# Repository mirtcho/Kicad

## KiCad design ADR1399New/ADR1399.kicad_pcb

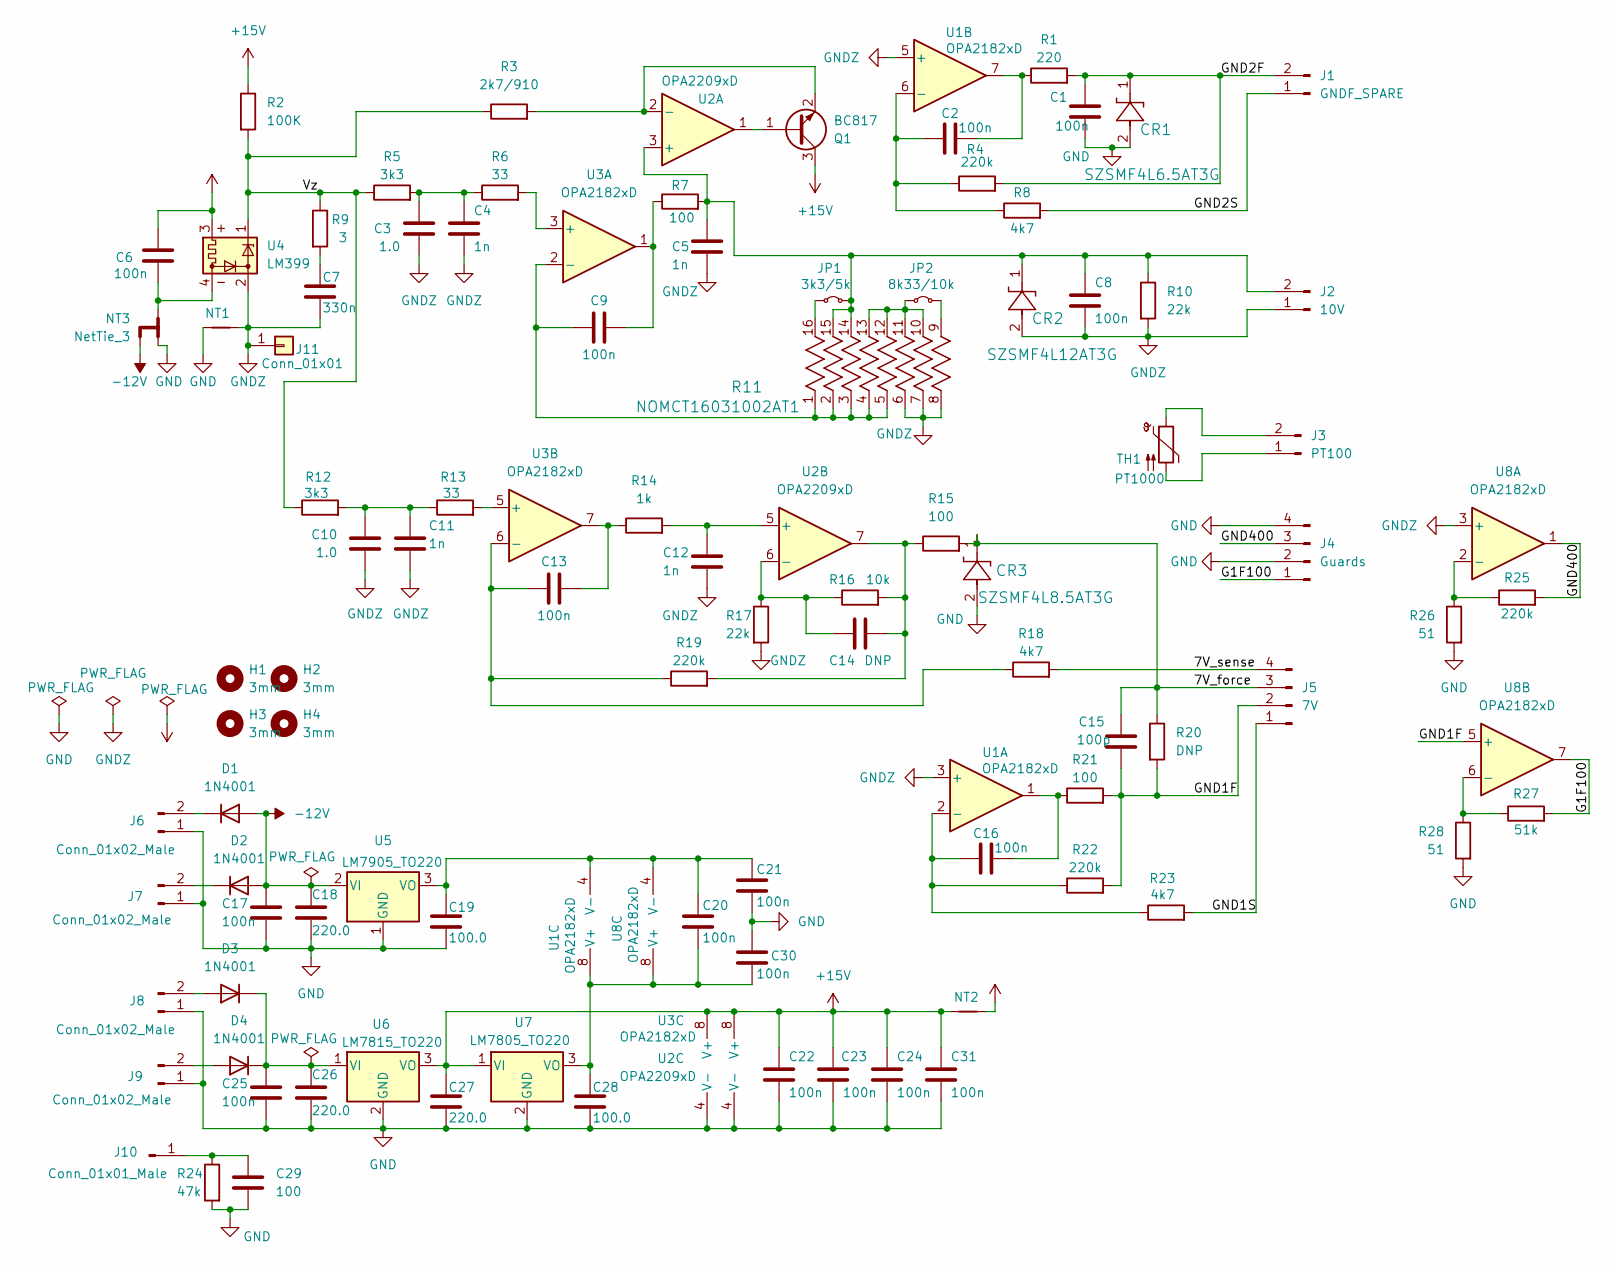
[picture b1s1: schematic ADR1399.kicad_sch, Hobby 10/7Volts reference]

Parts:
C1, C2, C6, C8, C9, C13, C16, C17, C25: 100n; C_1206_3216Metric_Pad1.33x1.80mm_HandSolder
C3, C10: 1.0; C_Rect_L7.2mm_W5.5mm_P5.00mm_FKS2_FKP2_MKS2_MKP2
C4, C11, C12: 1n; C_0805_2012Metric_Pad1.18x1.45mm_HandSolder
C5: 1n; C_1206_3216Metric_Pad1.33x1.80mm_HandSolder
C7: 330n; C_1206_3216Metric_Pad1.33x1.80mm_HandSolder
C14: DNP; C_0805_2012Metric_Pad1.18x1.45mm_HandSolder
C15: 100p; C_1206_3216Metric_Pad1.33x1.80mm_HandSolder
C18, C26, C27: 220.0; CP_Radial_D10.0mm_P7.50mm
C19, C28: 100.0; CP_EIA-3528-12_Kemet-T_HandSolder
C20, C21, C22, C23, C24, C30, C31: 100n; C_0805_2012Metric_Pad1.18x1.45mm_HandSolder
C29: 100; R_1206_3216Metric_Pad1.30x1.75mm_HandSolder
CR1: SZSMF4L6.5AT3G; ZDO_TPSMF4L5.0A_LTF-L
CR2: SZSMF4L12AT3G; ZDO_TPSMF4L5.0A_LTF-L
CR3: SZSMF4L8.5AT3G; ZDO_TPSMF4L5.0A_LTF-L
D1, D2, D3, D4: 1N4001; D_DO-41_SOD81_P10.16mm_Horizontal
H1, H2, H3, H4: 3mm; MountingHole_3.2mm_M3
J1: GNDF_SPARE; PinHeader_1x02_P2.54mm_Vertical
J2: 10V; PinHeader_1x02_P2.54mm_Vertical
J3: PT100; PinHeader_1x02_P2.54mm_Vertical
J4: Guards; PinHeader_2x02_P2.54mm_Vertical
J5: 7V; PinHeader_1x04_P2.54mm_Vertical
J6, J7, J8, J9: Conn_01x02_Male; PinHeader_1x02_P2.54mm_Horizontal
J10: Conn_01x01_Male; PinHeader_1x01_P1.00mm_Vertical
J11: Conn_01x01; SolderWire-1sqmm_1x01_D1.4mm_OD3.9mm
JP1: 3k3/5k; SolderJumper-2_P1.3mm_Bridged2Bar_RoundedPad1.0x1.5mm
JP2: 8k33/10k; SolderJumper-2_P1.3mm_Bridged2Bar_RoundedPad1.0x1.5mm
NT1, NT2: NetTie_2; NetTie-2_SMD_Pad2.0mm
NT3: NetTie_3; SolderJumper-3_P2.0mm_Open_TrianglePad1.0x1.5mm_NumberLabels
Q1: BC817; SOT-23
R1: 220; R_0805_2012Metric_Pad1.20x1.40mm_HandSolder
R2: 100K; R_0805_2012Metric_Pad1.20x1.40mm_HandSolder
R3: 2k7/910; R_1206_3216Metric_Pad1.30x1.75mm_HandSolder
R4, R19, R22, R25: 220k; R_0805_2012Metric_Pad1.20x1.40mm_HandSolder
R5, R12: 3k3; R_0805_2012Metric_Pad1.20x1.40mm_HandSolder
R6, R13: 33; R_0805_2012Metric_Pad1.20x1.40mm_HandSolder
R7, R15, R21: 100; R_0805_2012Metric_Pad1.20x1.40mm_HandSolder
R8, R18, R23: 4k7; R_0805_2012Metric_Pad1.20x1.40mm_HandSolder
R9: 3; R_1206_3216Metric_Pad1.30x1.75mm_HandSolder
R10, R17: 22k; R_0805_2012Metric_Pad1.20x1.40mm_HandSolder
R11: NOMCT16031002AT1; SOIC-16_3.9x9.9mm_P1.27mm
R14: 1k; R_0805_2012Metric_Pad1.20x1.40mm_HandSolder
R16: 10k; R_0805_2012Metric_Pad1.20x1.40mm_HandSolder
R20: DNP; R_0805_2012Metric_Pad1.20x1.40mm_HandSolder
R24: 47k; R_1206_3216Metric_Pad1.30x1.75mm_HandSolder
R26, R28: 51; R_0805_2012Metric_Pad1.20x1.40mm_HandSolder
R27: 51k; R_0805_2012Metric_Pad1.20x1.40mm_HandSolder
TH1: PT1000; PinHeader_1x02_P1.27mm_Vertical
U1, U3, U8: OPA2182xD; SOIC-8_3.9x4.9mm_P1.27mm
U2: OPA2209xD; SOIC-8_3.9x4.9mm_P1.27mm
U4: LM399; Analog_TO-46-4_ThermalShield
U5: LM7905_TO220; TO-220-3_Vertical
U6: LM7815_TO220; TO-220-3_Vertical
U7: LM7805_TO220; TO-220-3_Vertical

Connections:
+15V: C22.1, C23.1, C24.1, C27.1, C31.1, NT2.1, Q1.3 (C), R2.1, U2.8 (V+), U3.8 (V+), U6.3 (VO), U7.1 (VI)
+24V: C6.1, NT2.2, U4.3
-12V: C17.1, C18.1, D1.2 (A), D2.2 (A), NT3.3, U5.2 (VI)
/7V_force: C15.1, CR3.1, J5.3, R15.2, R20.1
/7V_sense: J5.4, R18.2
/G1F100: J4.1, R27.2, U8.7
/GND1F: C15.2, J5.2, R20.2, R21.2, R22.2, U8.5 (+)
/GND1S: J5.1, R23.2
/GND2F: C1.1, CR1.1, J1.2, R1.2, R4.2
/GND2S: J1.1, R8.2
/GND400: J4.3, R25.2, U8.1
/Vz: R2.2, R3.1, R5.1, R9.1, R12.1, U4.1
GND: C1.2, C17.2, C18.2, C19.2, C21.2, C22.2, C23.2, C24.2, C25.2, C26.2, C27.2, C28.2, C29.2, C30.1, C31.2, CR1.2, CR3.2, J4.2, J4.4, J6.1, J7.1, J8.1, J9.1, NT1.1, NT3.1, R24.2, R26.2, R28.2, U2.4 (V-), U3.4 (V-), U5.1 (GND), U6.2 (GND), U7.2 (GND)
GNDZ: C3.1, C4.2, C5.2, C7.2, C8.2, C10.1, C11.2, C12.2, CR2.2, J2.1, J11.1, NT1.2, R10.2, R11.6, R11.7, R11.8, R17.2, U1.3 (+), U1.5 (+), U4.2, U8.3 (+)
unnamed: C2.2, R1.1, U1.7
unnamed: C3.2, C4.1, R5.2, R6.1
unnamed: C6.2, NT3.2, U4.4
unnamed: C7.1, R9.2
unnamed: C9.1, R7.1, U3.1
unnamed: C10.2, C11.1, R12.2, R13.1
unnamed: C13.2, R14.1, U3.7
unnamed: C14.2, R15.1, R16.2, R19.2, U2.7
unnamed: C16.2, R21.1, U1.1
unnamed: D1.1 (K), J6.2
unnamed: D2.1 (K), J7.2
unnamed: D3.2 (A), J8.2
unnamed: C25.1, C26.1, D3.1 (K), D4.1 (K), U6.1 (VI)
unnamed: D4.2 (A), J9.2
unnamed: C5.1, C8.1, CR2.1, J2.2, JP1.2 (B), R7.2, R10.1, R11.14, R11.15, U2.3 (+)
unnamed: J3.1, TH1.2
unnamed: J3.2, TH1.1
unnamed: C29.1, J10.1, R24.1
unnamed: JP1.1 (A), R11.16
unnamed: JP2.1 (A), R11.10, R11.11, R11.12, R11.13
unnamed: JP2.2 (B), R11.9
unnamed: Q1.1 (B), U2.1
unnamed: Q1.2 (E), R3.2, U2.2 (-)
unnamed: C16.1, R22.1, R23.1, U1.2 (-)
unnamed: C2.1, R4.1, R8.1, U1.6 (-)
unnamed: C20.2, C28.1, C30.2, U1.8 (V+), U7.3 (VO), U8.8 (V+)
unnamed: C19.1, C20.1, C21.1, U1.4 (V-), U5.3 (VO), U8.4 (V-)
unnamed: C12.1, R14.2, U2.5 (+)
unnamed: C14.1, R16.1, R17.1, U2.6 (-)
unnamed: R6.2, U3.3 (+)
unnamed: C9.2, R11.1, R11.2, R11.3, R11.4, R11.5, U3.2 (-)
unnamed: R13.2, U3.5 (+)
unnamed: C13.1, R18.1, R19.1, U3.6 (-)
unnamed: R25.1, R26.1, U8.2 (-)
unnamed: R27.1, R28.1, U8.6 (-)

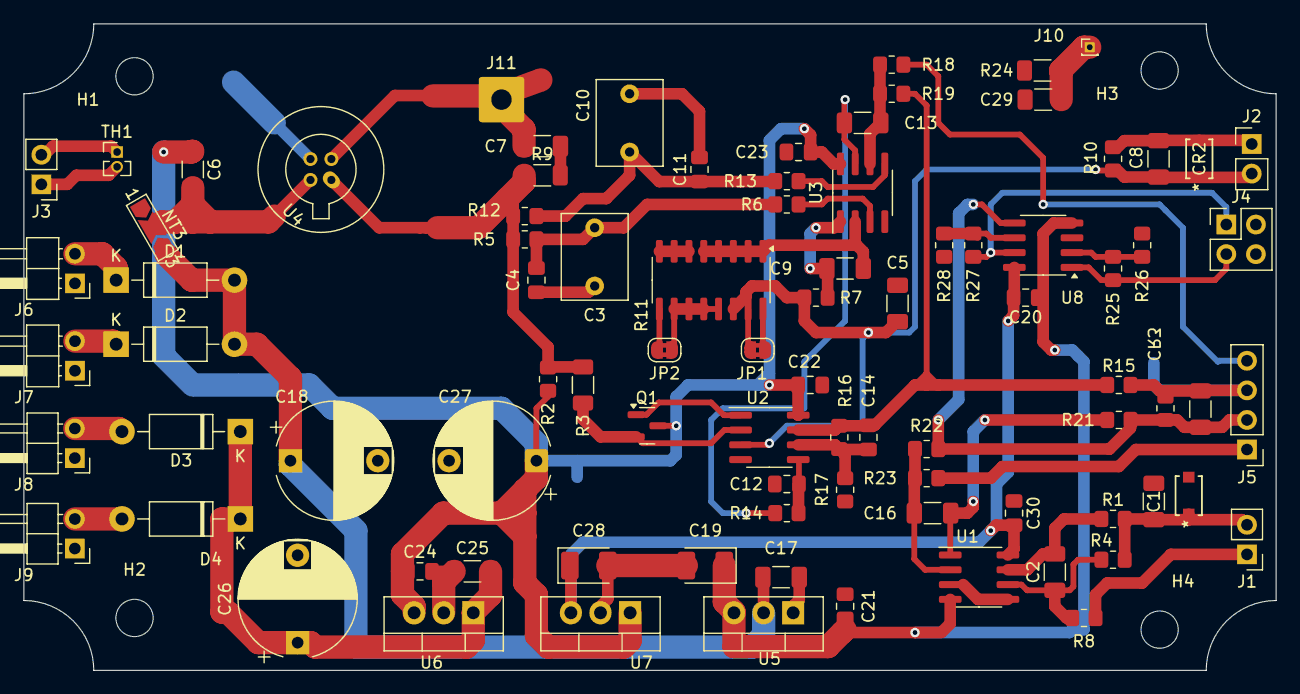
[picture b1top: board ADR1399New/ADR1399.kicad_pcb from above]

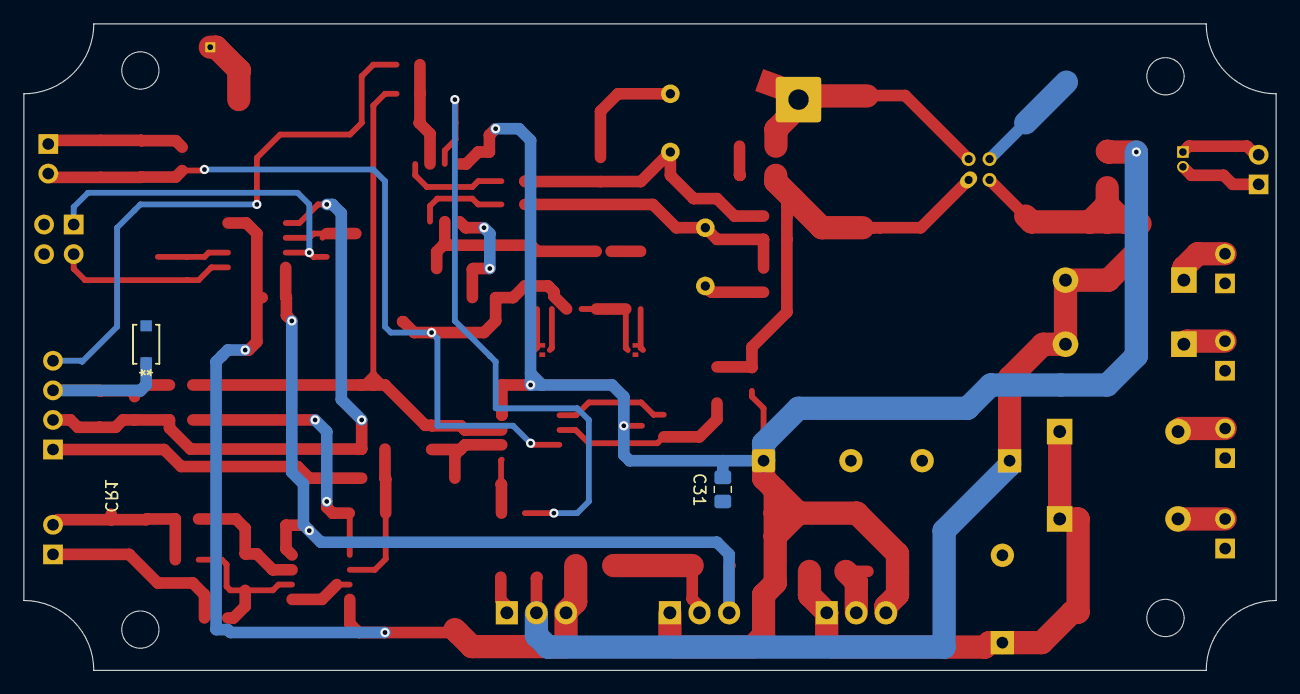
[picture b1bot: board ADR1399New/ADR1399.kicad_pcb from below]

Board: 4 copper layers, 107.5 x 55.5 mm, 96 parts (3 on the bottom side), 49 nets.

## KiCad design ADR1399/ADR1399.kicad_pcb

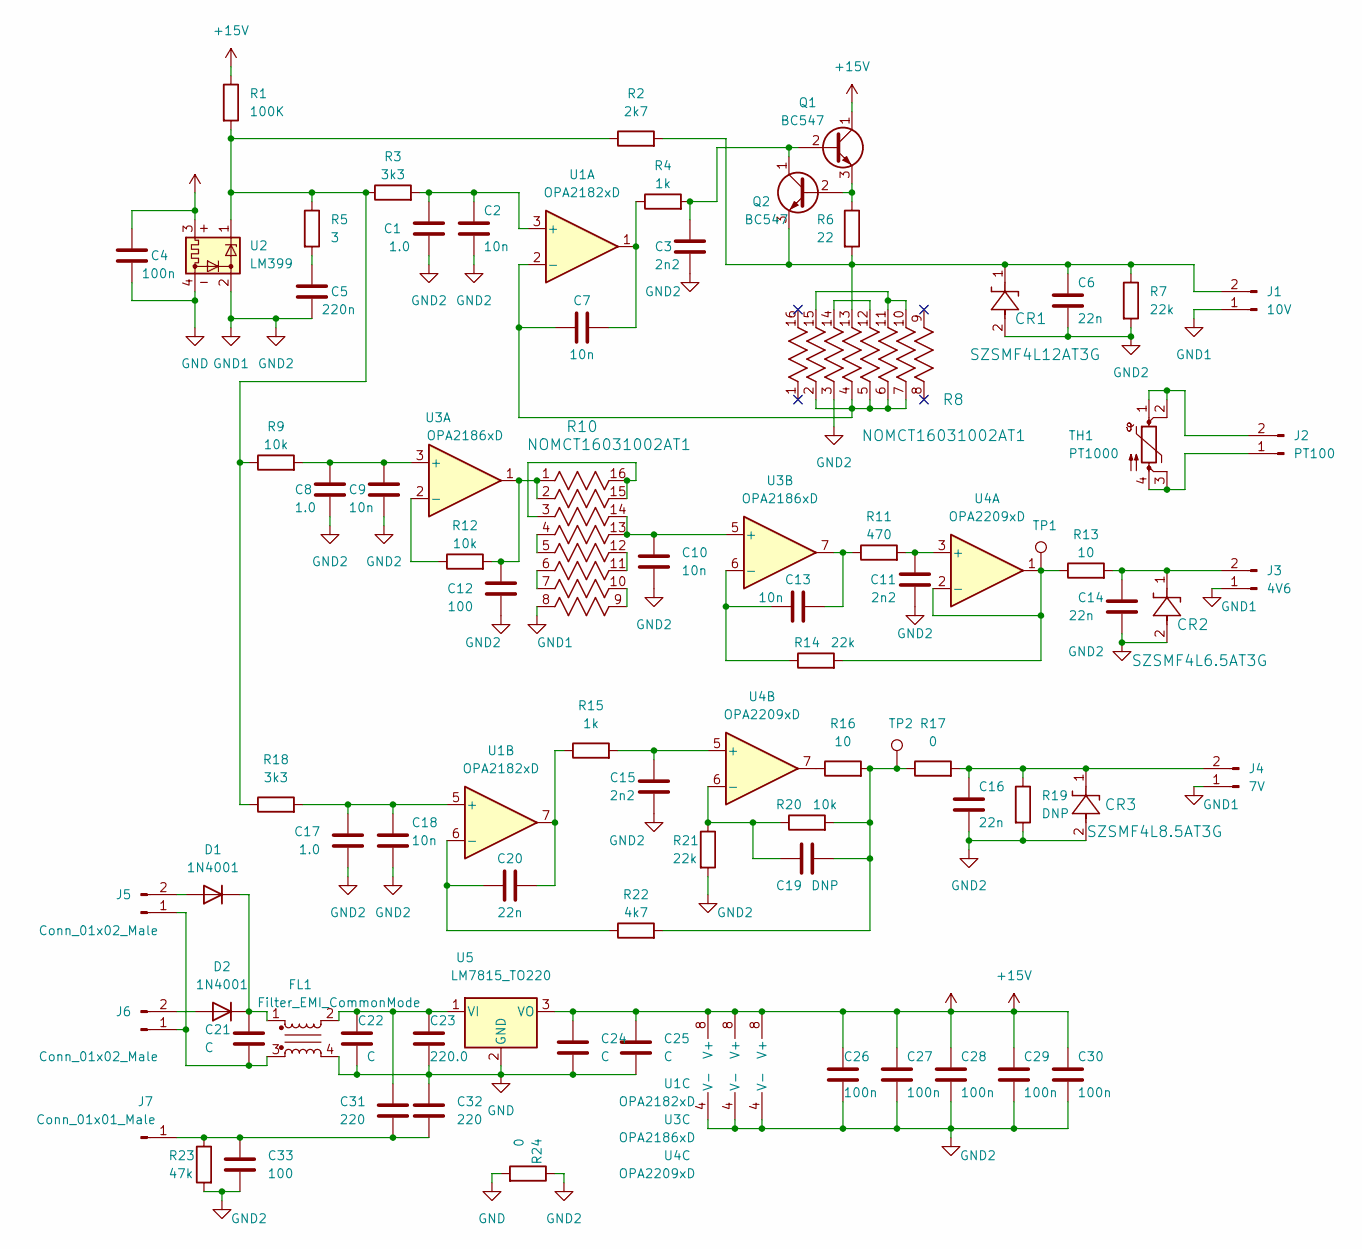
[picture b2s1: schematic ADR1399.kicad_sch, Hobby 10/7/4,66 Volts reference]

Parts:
C1, C8, C17: 1.0; C_Rect_L7.2mm_W4.5mm_P5.00mm_FKS2_FKP2_MKS2_MKP2
C2, C7, C9, C10, C13, C18: 10n; C_0805_2012Metric_Pad1.18x1.45mm_HandSolder
C3, C11, C15: 2n2; C_0805_2012Metric_Pad1.18x1.45mm_HandSolder
C4, C26, C27, C28, C29, C30: 100n; C_0805_2012Metric_Pad1.18x1.45mm_HandSolder
C5: 220n; C_0805_2012Metric_Pad1.18x1.45mm_HandSolder
C6, C14, C16, C20: 22n; C_0805_2012Metric_Pad1.18x1.45mm_HandSolder
C12: 100; C_0805_2012Metric_Pad1.18x1.45mm_HandSolder
C19: DNP; C_0805_2012Metric_Pad1.18x1.45mm_HandSolder
C21, C22, C24: C; C_1206_3216Metric
C23: 220.0; CP_Radial_D10.0mm_P7.50mm
C25: C; CP_Radial_D10.0mm_P7.50mm
C31, C32: 220; C_0805_2012Metric_Pad1.18x1.45mm_HandSolder
C33: 100; R_1206_3216Metric_Pad1.30x1.75mm_HandSolder
CR1: SZSMF4L12AT3G; ZDO_TPSMF4L5.0A_LTF
CR2: SZSMF4L6.5AT3G; ZDO_TPSMF4L5.0A_LTF
CR3: SZSMF4L8.5AT3G; ZDO_TPSMF4L5.0A_LTF
D1, D2: 1N4001; D_DO-41_SOD81_P10.16mm_Horizontal
FL1: Filter_EMI_CommonMode; FIL_RN102-2-02-1M1
J1: 10V; PinHeader_1x02_P2.54mm_Vertical
J2: PT100; PinHeader_1x02_P2.54mm_Vertical
J3: 4V6; PinHeader_1x02_P2.54mm_Vertical
J4: 7V; PinHeader_1x02_P2.54mm_Vertical
J5, J6: Conn_01x02_Male; PinHeader_1x02_P2.54mm_Horizontal
J7: Conn_01x01_Male; PinHeader_1x01_P1.00mm_Vertical
Q1, Q2: BC547; TO-92_Inline
R1: 100K; R_0805_2012Metric_Pad1.20x1.40mm_HandSolder
R2: 2k7; R_0805_2012Metric_Pad1.20x1.40mm_HandSolder
R3, R18: 3k3; R_0805_2012Metric_Pad1.20x1.40mm_HandSolder
R4, R15: 1k; R_0805_2012Metric_Pad1.20x1.40mm_HandSolder
R5: 3; R_0805_2012Metric_Pad1.20x1.40mm_HandSolder
R6: 22; R_0805_2012Metric_Pad1.20x1.40mm_HandSolder
R7, R14, R21: 22k; R_0805_2012Metric_Pad1.20x1.40mm_HandSolder
R8, R10: NOMCT16031002AT1; SO-16_3.9x9.9mm_P1.27mm
R9, R12, R20: 10k; R_0805_2012Metric_Pad1.20x1.40mm_HandSolder
R11: 470; R_0805_2012Metric_Pad1.20x1.40mm_HandSolder
R13, R16: 10; R_0805_2012Metric_Pad1.20x1.40mm_HandSolder
R17: 0; R_0805_2012Metric_Pad1.20x1.40mm_HandSolder
R19: DNP; R_0805_2012Metric_Pad1.20x1.40mm_HandSolder
R22: 4k7; R_0805_2012Metric_Pad1.20x1.40mm_HandSolder
R23: 47k; R_1206_3216Metric_Pad1.30x1.75mm_HandSolder
R24: 0; R_1206_3216Metric_Pad1.30x1.75mm_HandSolder
TH1: PT1000; PinHeader_2x02_P1.27mm_Vertical
TP1, TP2: TestPoint_Pad_1.5x1.5mm
U1: OPA2182xD; SOIC-8_3.9x4.9mm_P1.27mm
U2: LM399; Analog_TO-46-4_ThermalShield
U3: OPA2186xD; SOIC-8_3.9x4.9mm_P1.27mm
U4: OPA2209xD; SOIC-8_3.9x4.9mm_P1.27mm
U5: LM7815_TO220; TO-220-3_Vertical

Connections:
+15V: C4.1, C24.1, C25.1, C26.1, C27.1, C28.1, C29.1, C30.1, Q1.1 (C), R1.1, U1.8 (V+), U2.3, U3.8 (V+), U4.8 (V+), U5.3 (VO)
GND: C4.2, C22.2, C23.2, C24.2, C25.2, C32.1, FL1.4, R24.2, U2.4, U5.2 (GND)
GND1: C1.1, C2.2, C3.2, C5.2, C6.2, C8.2, C9.2, C10.2, C11.2, C12.1, C14.2, C15.2, C16.2, C17.1, C18.2, C26.2, C27.2, C28.2, C29.2, C30.2, C33.2, CR1.2, CR2.2, CR3.2, J1.1, J3.1, J4.1, R7.2, R8.3, R10.8, R19.2, R21.2, R23.2, R24.1, U1.4 (V-), U2.2, U3.4 (V-), U4.4 (V-)
unnamed: C5.1, R5.2
unnamed: C7.1, R4.1, U1.1
unnamed: C12.2, R10.1, R10.2, R12.2, U3.1
unnamed: C13.2, R11.1, U3.7
unnamed: C19.2, R16.2, R17.1, R20.2, R22.2, TP2.1
unnamed: C20.2, R15.1, U1.7
unnamed: D1.2 (A), J5.2
unnamed: C21.1, D1.1 (K), D2.1 (K), FL1.1
unnamed: D2.2 (A), J6.2
unnamed: C6.1, CR1.1, J1.2, Q2.3 (E), R2.2, R6.2, R7.1, R8.13
unnamed: J2.1, TH1.3, TH1.4
unnamed: J2.2, TH1.1, TH1.2
unnamed: C14.1, CR2.1, J3.2, R13.2
unnamed: C16.1, CR3.1, J4.2, R17.2, R19.1
unnamed: C21.2, FL1.3, J5.1, J6.1
unnamed: C31.2, C32.2, C33.1, J7.1, R23.1
unnamed: C3.1, Q1.2 (B), Q2.1 (C), R4.2
unnamed: Q1.3 (E), Q2.2 (B), R6.1
unnamed: R1.2, R2.1, R3.1, R5.1, R9.1, R18.1, U2.1
unnamed: R8.10, R8.11, R8.15
unnamed: R8.12, R8.14
unnamed: R10.4, R10.5
unnamed: R10.6, R10.7
unnamed: R10.9, R10.10
unnamed: R10.11, R10.12
unnamed: R10.3, R10.15, R10.16
unnamed: R16.1, U4.7
unnamed: C1.2, C2.1, R3.2, U1.3 (+)
unnamed: C7.2, R8.2, R8.4, R8.5, R8.6, R8.7, U1.2 (-)
unnamed: C17.2, C18.1, R18.2, U1.5 (+)
unnamed: C20.1, R22.1, U1.6 (-)
unnamed: C8.1, C9.1, R9.2, U3.3 (+)
unnamed: R12.1, U3.2 (-)
unnamed: C10.1, R10.13, R10.14, U3.5 (+)
unnamed: C13.1, R14.1, U3.6 (-)
unnamed: C11.1, R11.2, U4.3 (+)
unnamed: R13.1, R14.2, TP1.1, U4.1, U4.2 (-)
unnamed: C15.1, R15.2, U4.5 (+)
unnamed: C19.1, R20.1, R21.1, U4.6 (-)
unnamed: C22.1, C23.1, C31.1, FL1.2, U5.1 (VI)

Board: 4 copper layers, 80 parts (0 on the bottom side), 43 nets, no tracks yet.

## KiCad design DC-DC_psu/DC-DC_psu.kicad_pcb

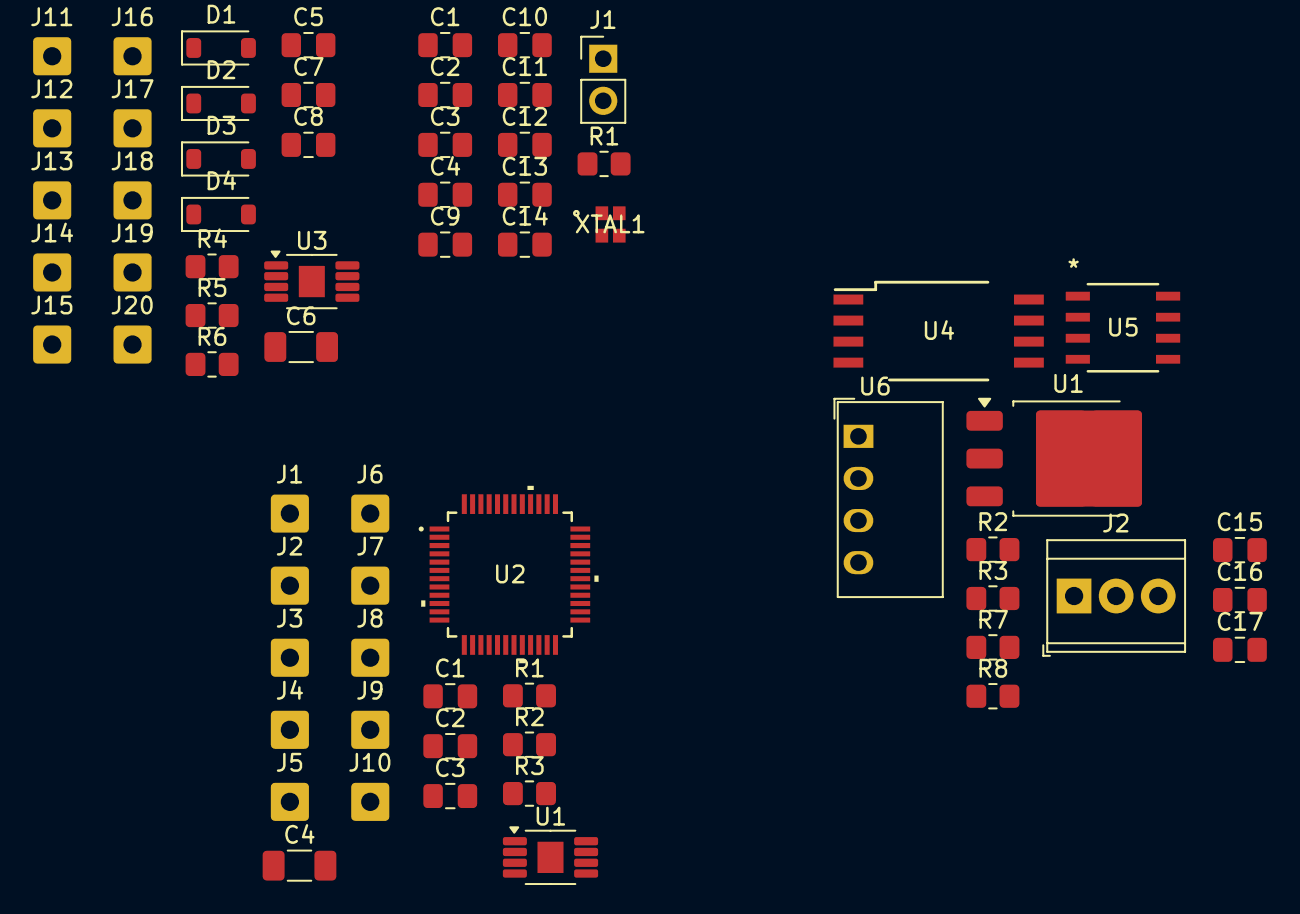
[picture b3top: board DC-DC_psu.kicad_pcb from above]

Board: 2 copper layers, 66 parts (0 on the bottom side), 28 nets, no tracks yet.

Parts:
C1: 4.7uF; C_0805_2012Metric_Pad1.18x1.45mm_HandSolder
C1#2, C2#2, C3, C5, C7, C8: C; C_0805_2012Metric_Pad1.18x1.45mm_HandSolder
C2, C3#2, C4#2, C9, C10: 100nF; C_0805_2012Metric_Pad1.18x1.45mm_HandSolder
C4, C6: C; C_1206_3216Metric_Pad1.33x1.80mm_HandSolder
C11, C12, C15: 1uF; C_0805_2012Metric_Pad1.18x1.45mm_HandSolder
C13, C14: 6.8pF; C_0805_2012Metric_Pad1.18x1.45mm_HandSolder
C16: 2.2uF; C_0805_2012Metric_Pad1.18x1.45mm_HandSolder
C17: 10nF; C_0805_2012Metric_Pad1.18x1.45mm_HandSolder
D1, D2, D3, D4: PMEG6010CEH; D_SOD-123
J1: RESET; PinHeader_1x02_P2.54mm_Vertical
J1#2, J2, J3, J4, J5, J6, J7, J8, J9, J10, J11, J12, J13, J14, J15, J16, J17, J18, J19, J20: Conn_01x01; SolderWire-0.5sqmm_1x01_D0.9mm_OD2.3mm
J2#2: Screw_Terminal_01x03; TerminalBlock_TE_282834-3_1x03_P2.54mm_Horizontal
R1: 10k; R_0805_2012Metric_Pad1.20x1.40mm_HandSolder
R1#2, R2#2, R3#2, R4, R5, R6: R; R_0805_2012Metric_Pad1.20x1.40mm_HandSolder
R2, R8: 0; R_0805_2012Metric_Pad1.20x1.40mm_HandSolder
R3, R7: 60; R_0805_2012Metric_Pad1.20x1.40mm_HandSolder
U1, U3: UCC25800; HVSSOP-8-1EP_3x3mm_P0.65mm_EP1.57x1.89mm
U1#2: TLV76133DCY; TO-252-3_TabPin2
U2: STM32G474CET6; LQFP48-7x7mm
U4: ISO1042DWV; DWV0008A
U5: TJA1462AT/0Z; SO8_SOT96-1_NXP
U6: CRE1S0305S3C; Converter_DCDC_Murata_CRE1xxxxxx3C_THT
XTAL1: NX2016AB-32MHZ ST2; NX2016AB_NDK

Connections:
+3.3V: C1.1, C2.1, C3#2.1, C4#2.1, C9.1, R1.1, R2.2, U2.1 (VBAT), U2.21 (VDDA), U2.24 (VDD), U2.36 (VDD), U2.48 (VDD), U4.1 (VCC1), U5.5 (VIO)
+5V: C15.2, R8.2, U1#2.3 (VI), U5.3 (VCC)
+24V: C3.1, C7.1, U1.8 (VCC), U3.8 (VCC)
GND: C1.2, C1#2.2, C2.2, C2#2.2, C3#2.2, C4#2.2, C5.2, C8.2, C9.2, C10.1, C11.1, C12.1, C13.2, C14.2, C15.1, C16.1, C17.1, J1.2, J2#2.2, R2#2.2, R3#2.2, R5.2, R6.2, U1.6 (GND), U1.9 (GND), U1#2.1 (GND), U2.19 (VSSA), U2.23 (VSS), U2.35 (VSS), U2.47 (VSS), U3.6 (GND), U3.9 (GND), U4.4 (GND1), U5.2 (GND), U6.3 (-VOUT), XTAL1.2, XTAL1.4
unnamed: C17.2, R3.1, R7.2
unnamed: D1.2 (A), D2.1 (K), J15.1
unnamed: D1.1 (K), D3.1 (K)
unnamed: D2.2 (A), D4.2 (A)
unnamed: D3.2 (A), D4.1 (K), J18.1
unnamed: C12.2, J1.1, R1.2, U2.7 (PG10-NRST)
unnamed: C4.2, J2.1, J2#2.1, R3.2, U5.7 (CANH)
unnamed: J2#2.3, R7.1, U5.6 (CANL)
unnamed: C2#2.1, C3.2, J4.1
unnamed: C6.2, J12.1
unnamed: C7.2, C8.1, J14.1
unnamed: R1#2.2, R2#2.1, U1.4 (OC/DT)
unnamed: R3#2.1, U1.5 (RT)
unnamed: C4.1, U1.7 (SW)
unnamed: C16.2, R2.1, U1#2.2 (VO)
unnamed: C1#2.1, R1#2.1, U1.3 (VREG)
unnamed: C13.1, U2.5 (PF0-OSC_IN), XTAL1.1
unnamed: C14.1, U2.6 (PF1-OSC_OUT), XTAL1.3
unnamed: C10.2, C11.2, U2.20 (VREF+)
unnamed: R4.2, R5.1, U3.4 (OC/DT)
unnamed: R6.1, U3.5 (RT)
unnamed: C6.1, U3.7 (SW)
unnamed: C5.1, R4.1, U3.3 (VREG)
unnamed: R8.1, U6.4 (+VOUT)

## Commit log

2025-01-11 push to github
2025-05-17 Push the local work from Ryzen5600G PC part 1
2025-05-17 push local work from Ryzen5600G PC part 2
2025-05-17 Push the local work from Ryzen5600G PC part 3
2025-06-08 Update KiCad project and add latest backups
2025-09-14 Update KiCad project and backup files- just before format R9 7900x SSD
